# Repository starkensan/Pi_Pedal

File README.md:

# USB-MIDI-Pedal

RP2040 Zero を使用して、ギター用フットスイッチやエクスプレッションペダルから  
USB-MIDI（CC / PC）メッセージを送信できるデバイスです。  
DAW ソフトやアンプシミュレーター（Amplitube / Helix Native など）で使用できます。

## Features
- USB MIDI（CC / PC）送信対応
- フットスイッチによる CC/PC 切り替え
- エクスプレッションペダル対応（アナログ入力）
- OLED による状態表示
- ノブによる直感的な操作
- ラッチ / モーメンタリ切り替え
- デバウンス処理付き
- コンパクトな RP2040 Zero ベース
- PCB 設計データ & 3D モデル付き

## Product image

## Hardware
- **Microcontroller:** RP2040 Zero  
- **Switches:** 1~（自由に拡張可能）  
- **Expression Pedal:** TRS（0〜3.3V）  
- **Display:** 0.96" OLED (I2C)
- **Rotary Encoder** EC11
- **ADC IC** MCP3421
- **その他:** 6.35mm ジャック、TRS、PCB（KiCad）、3Dプリントケース

KiCad の設計データは `hardware/kicad/`、PDF やガーバーファイルなどの生成物は `hardware/exports/`、3D モデルは `3d-models/` に配置しています。

## Software
- **Language:** C++ / Arduino Core RP2040  
- **USB MIDI:** TinyUSB  
- **スイッチ管理:** デバウンス、ラッチ/モーメンタリ対応  
- **表示:** Adafruit SSD1306@^2.5.15

ソフトウェアの構成、MIDI処理、設定メニューの状態遷移は[アーキテクチャドキュメント](docs/ARCHITECTURE.md)を参照してください。

## CI

GitHub Actions で PlatformIO ビルドを自動実行しています。

- ワークフロー: `PlatformIO Build`
- 対象: `pull_request`, `develop` への `push`
- ビルド対象: `pico`, `pico-debug`

PR レビュー時は、`PlatformIO Build` が成功していることを確認してください。

## Build & Upload (CUI / PlatformIO CLI)

本ドキュメントでは、VS Code を使用せず、  
**CUI（ターミナル）から PlatformIO CLI を用いて**  
ビルドおよび RP2040 Zero への書き込みを行う手順を説明します。

### 事前準備

- Python 3.x
- PlatformIO Core（CLI）

#### PlatformIO CLI のインストール

```bash
pip install platformio
````

インストール確認：

```bash
pio --version
```

### ビルド（env:pico）

本プロジェクトでは、通常動作用に `env:pico` を使用します。

```bash
pio run -e pico
```

ビルドが成功すると、以下のディレクトリに成果物が生成されます。

```
.pio/build/pico/
```

### 書き込み（USB / picotool）

RP2040 Zero を USB 接続した状態で、以下を実行します。

```bash
pio run -e pico -t upload
```

### 書き込みに失敗する場合（BOOTSEL モード）

1. RP2040 Zero の **BOOT** ボタンを押しながら USB 接続
2. PC に `RPI-RP2` ドライブが表示されることを確認
3. 再度アップロードを実行

```bash
pio run -e pico -t upload
```

### UF2 ファイルを手動で書き込む方法

PlatformIO による自動書き込みができない場合は、
生成された UF2 ファイルを直接コピーすることで書き込み可能です。

UF2 ファイルの場所：

```
.pio/build/pico/firmware.uf2
```

この `firmware.uf2` を `RPI-RP2` ドライブへ
ドラッグ＆ドロップしてください。

### シリアルモニタ（ログ確認）

```bash
pio device monitor -e pico
```

※ ボーレートは `platformio.ini` にて `115200` に設定されています。

### 接続デバイス一覧の確認

```bash
pio device list
```

### 補足：env の使い分け

* `env:pico`
  通常動作用（USB MIDI / picotool）

* `env:pico-debug`
  CMSIS-DAP を使用したデバッグ用

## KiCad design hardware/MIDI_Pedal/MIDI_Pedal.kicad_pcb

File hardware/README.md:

# Hardware

ハードウェア関連ファイルは、編集元と生成物を分けて配置します。

## Directory

- `kicad/`: KiCad の編集元プロジェクト、回路図、PCB、フットプリント
- `exports/pdf/`: 回路図や PCB などの PDF 出力
- `exports/gerber/`: 基板製造用のガーバー、ドリル、製造用パッケージ

## Notes

`exports/gerber/MIDI_Pedal/current/` は KiCad から出力したガーバーファイルです。

`exports/gerber/MIDI_Pedal/fabrication-package/` は、発注や共有に使う製造用パッケージを置く場所です。

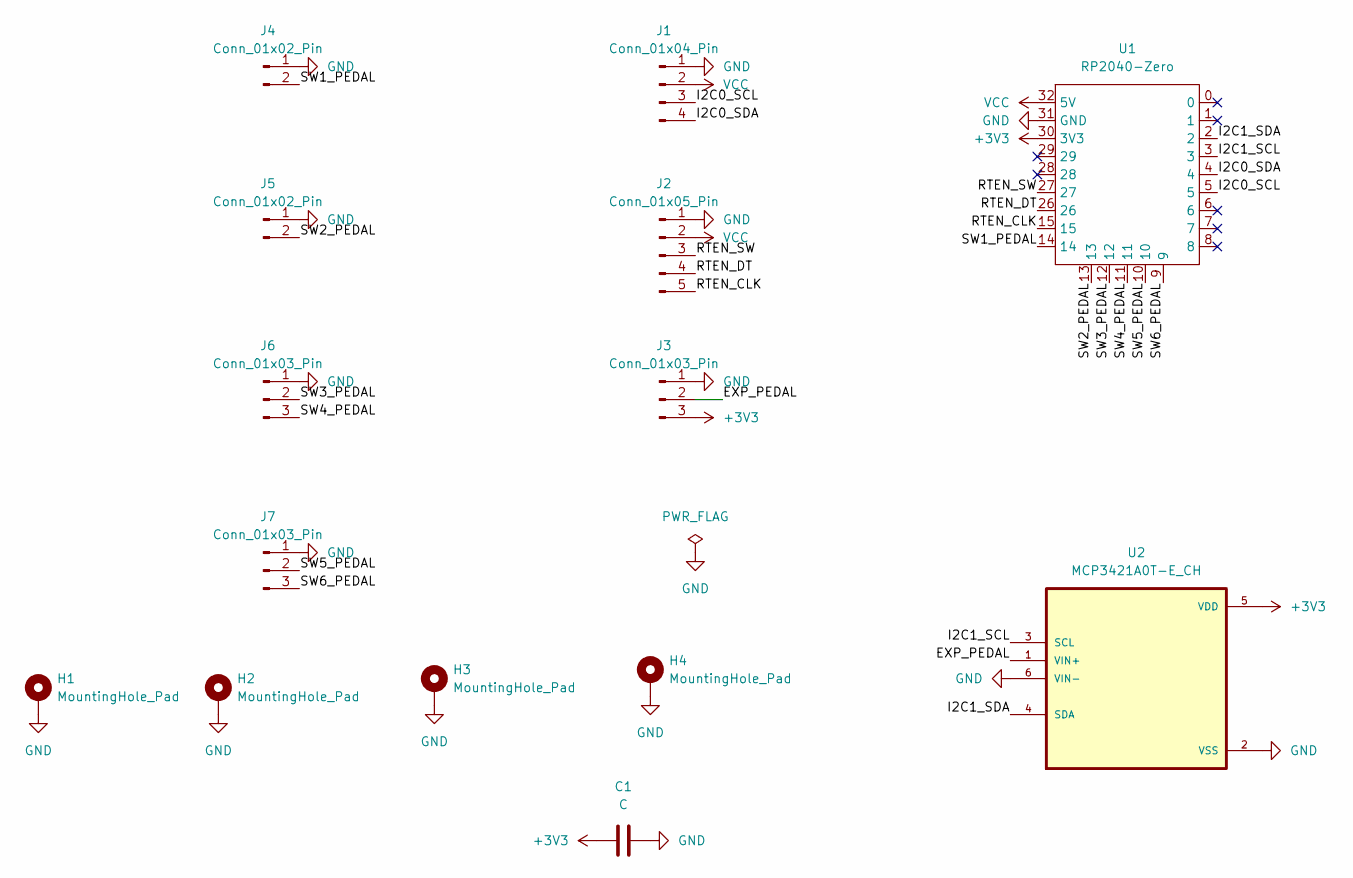
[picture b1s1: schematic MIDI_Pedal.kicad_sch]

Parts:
C1: C; C_0805_2012Metric
H1, H2, H3, H4: MountingHole_Pad; MountingHole_3.2mm_M3_Pad_Via
J1: Conn_01x04_Pin; PinHeader_1x04_P2.54mm_Vertical
J2: Conn_01x05_Pin; PinHeader_1x05_P2.54mm_Vertical
J3, J6, J7: Conn_01x03_Pin; PinHeader_1x03_P2.54mm_Vertical
J4, J5: Conn_01x02_Pin; PinHeader_1x02_P2.54mm_Vertical
U1: RP2040-Zero; RP2040-Zero-SMD
U2: MCP3421A0T-E_CH; SOT-23-6_Handsoldering

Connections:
+3V3: C1.1, J3.3, U1.30 (3V3), U2.5 (VDD)
/EXP_PEDAL: J3.2, U2.1 (VIN+)
/I2C0_SCL: J1.3, U1.5
/I2C0_SDA: J1.4, U1.4
/I2C1_SCL: U1.3, U2.3 (SCL)
/I2C1_SDA: U1.2, U2.4 (SDA)
/RTEN_CLK: J2.5, U1.15
/RTEN_DT: J2.4, U1.26
/RTEN_SW: J2.3, U1.27
/SW1_PEDAL: J4.2, U1.14
/SW2_PEDAL: J5.2, U1.13
/SW3_PEDAL: J6.2, U1.12
/SW4_PEDAL: J6.3, U1.11
/SW5_PEDAL: J7.2, U1.10
/SW6_PEDAL: J7.3, U1.9
GND: C1.2, H1.1, H2.1, H3.1, H4.1, J1.1, J2.1, J3.1, J4.1, J5.1, J6.1, J7.1, U1.31 (GND), U2.2 (VSS), U2.6 (VIN-)
VCC: J1.2, J2.2, U1.32 (5V)

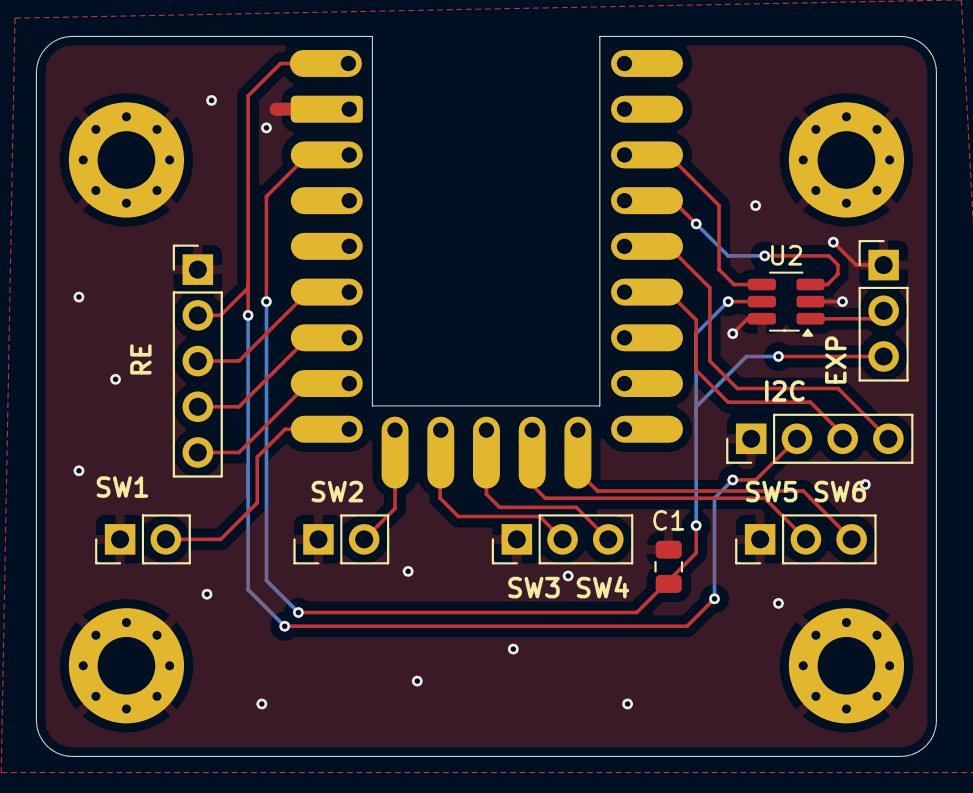
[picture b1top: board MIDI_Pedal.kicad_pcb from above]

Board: 2 copper layers, 50.0 x 40.0 mm, 14 parts (0 on the bottom side), 17 nets.

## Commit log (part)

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2025-09-14 USBでフットペダルやエクスプレッションペダルを操作できるようにする
2025-09-14 [環境] platformio.initの変更 - 書き込みができるように変更
2025-09-14 [修正] ディレクトリの整理とDrawMenuの実装 - ディレクトリをDriverとlibに分割 - mainに処理内容を書かないようにDrawMenuを実装
2025-09-14 [追加] 画面遷移の実装
2025-09-16 [追加] 画面遷移の実装 - 画面遷移を管理するクラスのDisplayStateを追加
2025-10-20 [変更] ファイル構成の変更
    - ハードウェアを直接操作するdriverディレクトリの追加
    - driverをラッピングするinterfacesディレクトリの追加
    - interfacesまたはdriverを使用し制御するcontrolディレクトリの追加
2025-10-20 [Add] メニュー描画をするクラスの追加
2025-10-21 [Add] メニュー描画をするクラスの追加
    - DrawDisplayクラスの追加
    - DebugLogによるデバック出力の追加
    - DrawDisplayの単体テストの追加
2025-10-21 [Fix] ペダル監視クラスの修正
    - Pedal.hではmidiを扱わないように修正
    - Pedal.hのテストを追加
2025-10-21 [Fix] ExpPedalクラスの修正
    - ExpPedal.hではmidiを扱わないように修正
    - ExpPedal.hのテストを追加
2025-10-21 [Fix] ペダル監視クラスの修正
    - RotaryEncoder.hのテストの追加
2025-10-21 [Fix] ハードウェアコントローラーのインターフェイス化
    - DrawDisplayのインターフェイスクラスのIDisplayの追加
    - ExpPedalのインターフェイスクラスのIExpPedalの追加
2025-10-25 [Add] EepromStorageクラスの追加
    - 設定保存用のEepromStrageクラスの追加
    - テスト実行時リンカエラーが出る現象の修正
2025-10-25 [Add] EepromStorageクラスの追加
2025-10-25 [Add] USB MIDIラッピングクラスの実装 refs #1221
2025-10-26 [Fix] ハードウェアコントローラーのインターフェイス化
    - 各ドライバライブラリの抽象化ライブラリの追加
2025-10-27 [Fix] ハードウェアコントローラーのインターフェイス化
2025-10-27 [Add] 設定管理クラスの追加
2025-10-30 [Fix] ペダル監視クラスを複数のペダルに対応
2025-11-02 [Fix] 設定管理クラスの修正
    - crc機能の削除
2025-11-04 [Add] PedalsControllerクラスの追加
2025-11-21 [Fix] SettingControllerのペダル設定が反映されない現象の修正
2025-11-30 [Fix] 設定管理クラスのCRCの削除
2025-12-02 [Add] PedalsControllerクラスの追加 - ペダル管理用のクラスを追加 - セッティングバージョンを1に変更
2025-12-02 [ADD]PCB-CADファイルの追加
2025-12-02 [Release] V0.1.0
2025-12-03 [ADD]SettingsManagerの排他制御の追加
    - PedalControllerとメニュー描画でSettingsManagerを使うことを考慮して排他制御の追加
2025-12-03 [ADD]メニュー管理クラスの追加
2025-12-05 [Fix]設定管理クラスの設定項目の名前空間化
    - Settings,PedalSettings, SwitchBehavior, PedalModeを名前空間SettingsDefsに移動
    - ioメソッドの追加
2025-12-16 [ADD] メニュー描画クラスの追加
2025-12-18 [Add]メニュー制御クラスの追加
2025-12-19 [Fix] [ADD]メニュー管理クラスのパラーメーター管理構造体の変更
2025-12-21 [Fix]メニュー管理クラスでインデックスの管理もするように修正
2025-12-21 [Fix] メニュー描画クラスをMenuManagerの修正に適用
2025-12-22 [Fix[ メニュー描画クラスをコンストラクタでパラーメーターを渡すように修正
    - MenuMangerの初期化時はパラーメーターIDで起動画面を指定するように変更
2025-12-22 [Fix] 設定管理クラスの初期化タイミングの調整
2025-12-22 [Add] mainへのメニューの実装
2025-12-22 [Add] メインメニューでPCの現在の番号を表示
2025-12-25 [Update] Readmeのセットアップ手順の追加
2026-04-15 Ignore Codex local file
2026-04-15 Document branch naming convention
2026-04-15 docs: コミットメッセージ規約を追加
2026-04-15 docs: PRタイトル規約を追加
2026-04-15 chore: 生成物のignore設定を追加
2026-04-15 docs: PRテンプレートを追加
2026-04-15 docs: ハードウェア配置説明を修正
2026-04-16 chore: KiCadバックアップを管理対象から削除
2026-04-16 chore: ハードウェア構成を整理
2026-04-16 chore: 共通ヘッダをincludeに統一
2026-04-16 refactor: アプリモジュール配置を整理
2026-04-16 chore: PlatformIOビルドCIを追加
2026-04-16 fix: CIで共通ヘッダの探索パスを補完
2026-04-16 chore: PlatformIOキャッシュ戦略を追加
2026-04-16 docs: READMEにCI運用情報を追加
2026-04-16 chore: CIをソース変更時のみ実行
2026-04-29 Add Codex CLI command documentation
2026-04-29 chore: PlatformIOビルドCI運用を補強 #58
2026-04-29 test: manual/ciテスト分類ルールを追加 #64
2026-04-29 test: nativeテスト環境を追加 #66
2026-04-29 test: SettingsManagerをnativeテスト可能に分離 #65
2026-04-29 refactor: 設定依存をSettingsStoreへ分離 #71
